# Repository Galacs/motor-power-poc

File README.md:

# Motor Power POC

Motor Power POC board made to test power protection circuits (OCP, UVLO, OVL, RPP...), high current step-down power supply design, rf switch connectors, external FETs H-bridge and power muxes.

## IC List

- ESP32-S3Fx (Main MCU)
- QRE1113 (reflectance sensor)
- LM74502H (Vin RPP)
- TPS56A37 (12v Vout 10A)
- TPS5430 (5v Vout 2.5A)
- LDL212 (3v3 LDO)
- CJ431 (3v shunt reference)
- TPS2121 (5v power mux)
- DRV8701 (H-bridge gate driver)
- SIS412DN-T1-GE3 (10A MOSFET)

## Top preview

## Preview 3d render

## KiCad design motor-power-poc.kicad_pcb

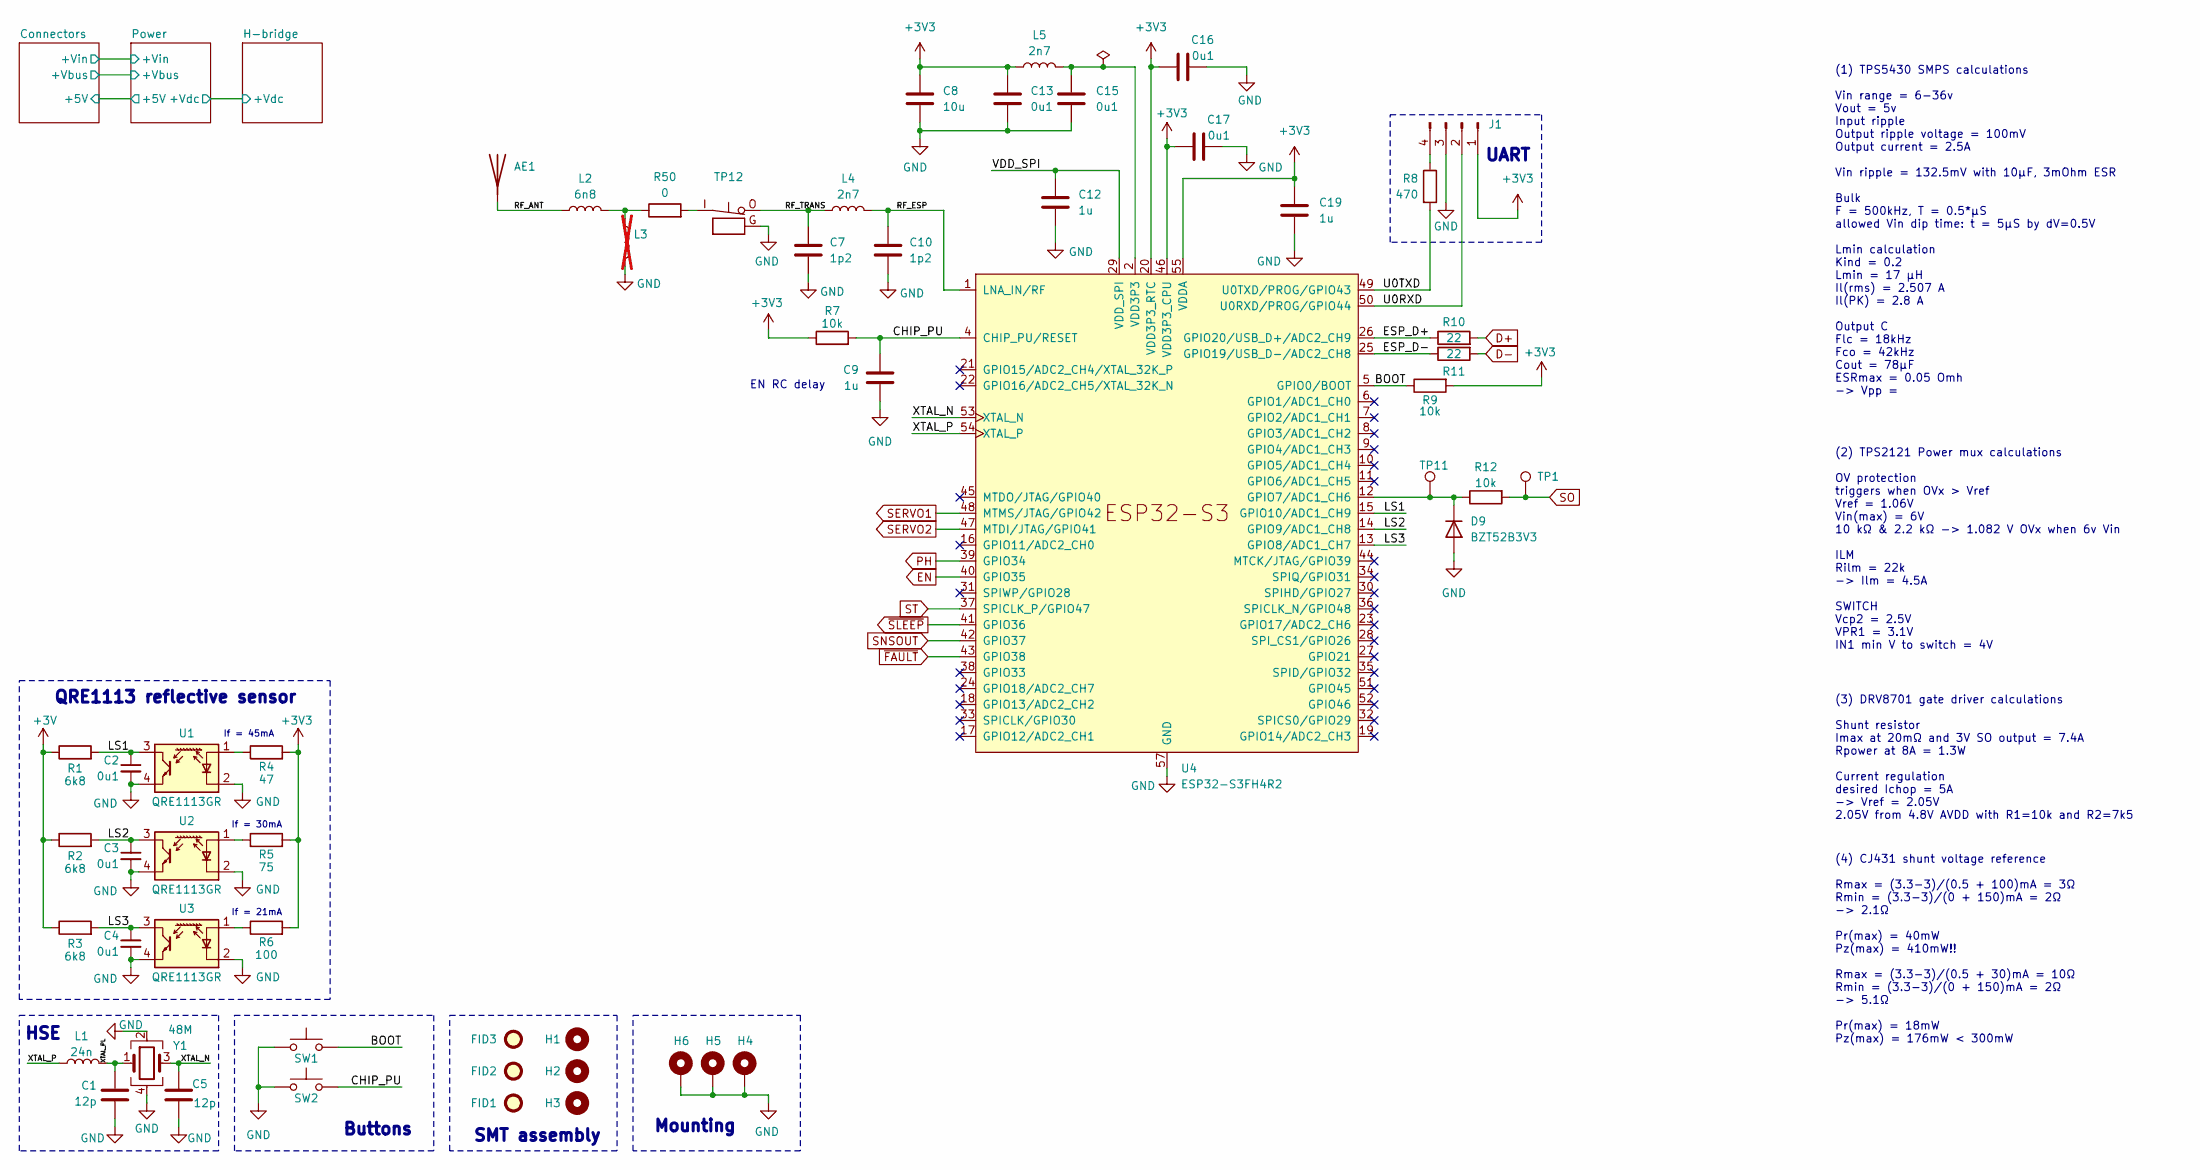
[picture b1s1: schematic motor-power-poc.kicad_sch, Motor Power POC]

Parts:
AE1: Antenna; Johanson_2450AT18x100; Manufacturer Part Number RFANT3216120A5T; JLCPCB Part # C127629
C1, C5: 12p; C_0402_1005Metric; Manufacturer Part Number 0402CG120J500NT; JLCPCB Part # C1547
C2, C3, C4, C13, C15, C16, C17: 0u1; C_0402_1005Metric; Manufacturer Part Number CL05B104KB54PNC; JLCPCB Part # C307331
C7, C10: 1p2; C_0402_1005Metric; Manufacturer Part Number GJM1555C1H1R2WB01D; JLCPCB Part # C76899
C8: 10u; C_0402_1005Metric; Manufacturer Part Number CL05A106MQ5NUNC; JLCPCB Part # C15525
C9, C12, C19: 1u; C_0402_1005Metric; Manufacturer Part Number CL05A105KA5NQNC; JLCPCB Part # C52923
D9: BZT52B3V3; D_SOD-123; Manufacturer Part Number BZT52B3V3; JLCPCB Part # C19077392
FID1, FID2, FID3: Fiducial; Fiducial_1mm_Mask2mm
H1, H2, H3: MountingHole; ToolingHole_1.152mm
H4, H5, H6: MountingHole_Pad; MountingHole_2.2mm_M2_Pad_Via
J1: Conn_01x04_Pin; PinHeader_1x04_P2.54mm_Vertical
L1: 24n; L_0402_1005Metric; Manufacturer Part Number LQW15AN24NG00D; JLCPCB Part # C167472
L2: 6n8; L_0402_1005Metric; Manufacturer Part Number LQG15HS6N8J02D; JLCPCB Part # C77110
L3: L; L_0402_1005Metric; not fitted
L4, L5: 2n7; L_0402_1005Metric; Manufacturer Part Number LQG15HS2N7S02D; JLCPCB Part # C77108
R1, R2, R3: 6k8; R_0603_1608Metric; Manufacturer Part Number 0603WAF6801T5E; JLCPCB Part # C23212
R4: 47; R_0603_1608Metric; Manufacturer Part Number 0603WAF470JT5E; JLCPCB Part # C23182
R5: 75; R_0603_1608Metric; Manufacturer Part Number 0603WAF750JT5E; JLCPCB Part # C4275
R6: 100; R_0603_1608Metric; Manufacturer Part Number 0603WAF1000T5E; JLCPCB Part # C22775
R7, R9, R12: 10k; R_0402_1005Metric; Manufacturer Part Number 0402WGF1002TCE; JLCPCB Part # C25744
R8: 470; R_0402_1005Metric; Manufacturer Part Number 0402WGF4700TCE; JLCPCB Part # C25117
R10, R11: 22; R_0402_1005Metric; Manufacturer Part Number 0402WGF220JTCE; JLCPCB Part # C25092
R50: 0; R_0402_1005Metric; Manufacturer Part Number 0402WGF0000TCE; JLCPCB Part # C17168
SW1, SW2: SW_Push; SW_SPST_TS-1088-xR020; Manufacturer Part Number TS-1088-AR02016; JLCPCB Part # C720477
TP1, TP11: TestPoint; TestPoint_Keystone_5015_Micro_Mini; Manufacturer Part Number 5015; JLCPCB Part # C2906768
TP12: RF_switch_connector; Murata_MM8030-26102610; Manufacturer Part Number MM8030-2610RK0; JLCPCB Part # C91632
U1, U2, U3: QRE1113GR; OnSemi_CASE100CY; Manufacturer Part Number QRE1113GR; JLCPCB Part # C232862
U4: ESP32-S3FH4R2; QFN-56-1EP_7x7mm_P0.4mm_EP4x4mm_ThermalVias; Manufacturer Part Number ESP32-S3FH4R2; JLCPCB Part # C3013940
Y1: 48M; Crystal_SMD_2016-4Pin_2.0x1.6mm; Manufacturer Part Number R940000096; JLCPCB Part # C7206306

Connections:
+3V: R1.1, R2.1, R3.1; also elsewhere on the board
+3V3: C8.1, C13.1, C16.1, C17.1, C19.1, J1.1, L5.1, R4.2, R5.2, R6.2, R7.1, R9.2, U4.20 (VDD3P3_RTC), U4.46 (VDD3P3_CPU), U4.55 (VDDA), U4.56 (VDDA); also elsewhere on the board
/BOOT: R9.1, SW1.2, U4.5 (GPIO0/BOOT)
/CHIP_PU: C9.1, R7.2, SW2.2, U4.4 (CHIP_PU/RESET)
/ESP_D+: R10.1, U4.26 (GPIO20/USB_D+/ADC2_CH9)
/ESP_D-: R11.1, U4.25 (GPIO19/USB_D-/ADC2_CH8)
/LS1: C2.1, R1.2, U1.3, U4.15 (GPIO10/ADC1_CH9)
/LS2: C3.1, R2.2, U2.3, U4.14 (GPIO9/ADC1_CH8)
/LS3: C4.1, R3.2, U3.3, U4.13 (GPIO8/ADC1_CH7)
/RF_ANT: AE1.1 (A), L2.1
/RF_ESP: C10.1, L4.2, U4.1 (LNA_IN/RF)
/RF_TRANS: C7.1, L4.1, TP12.O
/U0RXD: J1.2, U4.50 (U0RXD/PROG/GPIO44)
/U0TXD: R8.2, U4.49 (U0TXD/PROG/GPIO43)
/VDD_SPI: C12.1, U4.29 (VDD_SPI)
/XTAL_N: C5.1, U4.53 (XTAL_N), Y1.3
/XTAL_P: L1.1, U4.54 (XTAL_P)
/XTAL_PL: C1.2, L1.2, Y1.1
D+: R10.2; also elsewhere on the board
D-: R11.2; also elsewhere on the board
EN: U4.40 (GPIO35); also elsewhere on the board
GND: C1.1, C2.2, C3.2, C4.2, C5.2, C7.2, C8.2, C9.2, C10.2, C12.2, C13.2, C15.2, C16.2, C17.2, C19.2, D9.2 (A), H4.1, H5.1, H6.1, J1.3, L3.2, SW1.1, SW2.1, TP12.G, U1.2 (K), U1.4, U2.2 (K), U2.4, U3.2 (K), U3.4, U4.57 (GND), Y1.2, Y1.4; also elsewhere on the board
unnamed: D9.1 (K), R12.1, TP11.1, U4.12 (GPIO7/ADC1_CH6)
unnamed: J1.4, R8.1
unnamed: L2.2, L3.1, R50.1
unnamed: R50.2, TP12.I
unnamed: R4.1, U1.1 (A)
unnamed: R5.1, U2.1 (A)
unnamed: R6.1, U3.1 (A)
PH: U4.39 (GPIO34); also elsewhere on the board
SERVO1: U4.48 (MTMS/JTAG/GPIO42); also elsewhere on the board
SERVO2: U4.47 (MTDI/JTAG/GPIO41); also elsewhere on the board
SNSOUT: U4.42 (GPIO37); also elsewhere on the board
SO: R12.2, TP1.1; also elsewhere on the board
ST: U4.37 (SPICLK_P/GPIO47); also elsewhere on the board
VDD3P3: C15.1, L5.2, U4.2 (VDD3P3), U4.3 (VDD3P3)
~FAULT: U4.43 (GPIO38); also elsewhere on the board
~SLEEP: U4.41 (GPIO36); also elsewhere on the board

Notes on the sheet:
SMT assembly
Mounting
If = 30mA
Buttons
EN RC delay
QRE1113 reflective sensor
If = 45mA
HSE
UART
If = 21mA
(3) DRV8701 gate driver calculations Shunt resistor Imax at 20mΩ and 3V SO output = 7.4A Rpower at 8A = 1.3W Current regulation desired Ichop = 5A -> Vref = 2.05V 2.05V from 4.8V AVDD with R1=10k and R2=7k5
(1) TPS5430 SMPS calculations Vin range = 6-36v Vout = 5v Input ripple Output ripple voltage = 100mV Output current = 2.5A Vin ripple = 132.5mV with 10µF, 3mOhm ESR Bulk F = 500kHz, T = 0.5*µS allowed Vin dip time: t = 5µS by dV=0.5V Lmin calculation Kind = 0.2 Lmin = 17 µH Il(rms) = 2.507 A Il(PK)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
(4) CJ431 shunt voltage reference Rmax = (3.3-3)/(0.5 + 100)mA = 3Ω Rmin = (3.3-3)/(0 + 150)mA = 2Ω -> 2.1Ω Pr(max) = 40mW Pz(max) = 410mW!! Rmax = (3.3-3)/(0.5 + 30)mA = 10Ω Rmin = (3.3-3)/(0 + 150)mA = 2Ω -> 5.1Ω Pr(max) = 18mW Pz(max) = 176mW < 300mW
(2) TPS2121 Power mux calculations OV protection triggers when OVx > Vref Vref = 1.06V Vin(max) = 6V 10 kΩ & 2.2 kΩ -> 1.082 V OVx when 6v Vin ILM Rilm = 22k -> Ilm = 4.5A SWITCH Vcp2 = 2.5V VPR1 = 3.1V IN1 min V to switch = 4V

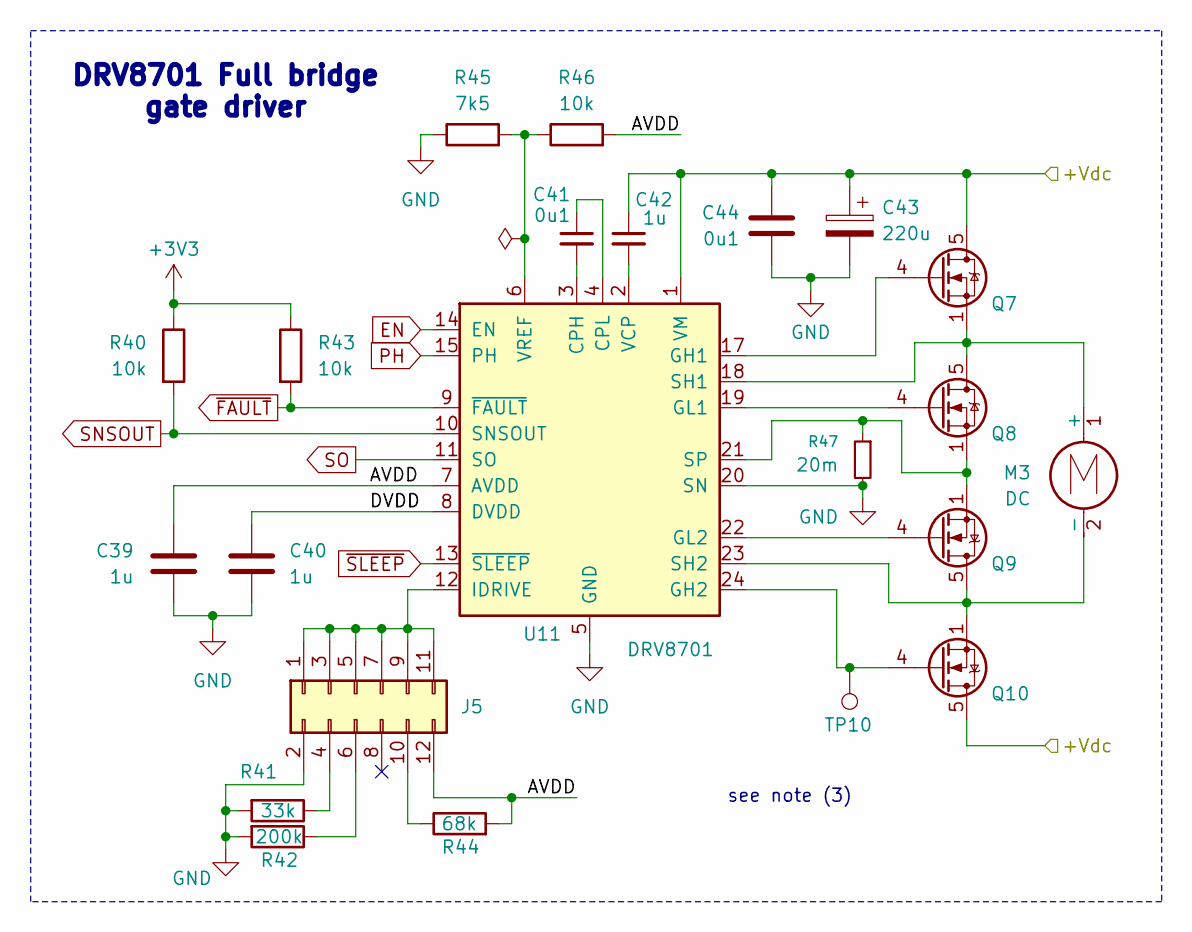
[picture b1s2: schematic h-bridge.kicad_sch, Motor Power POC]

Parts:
C39, C40, C42: 1u; C_0402_1005Metric; Manufacturer Part Number CL05A105KA5NQNC; JLCPCB Part # C52923
C41, C44: 0u1; C_0402_1005Metric; Manufacturer Part Number CL05B104KB54PNC; JLCPCB Part # C307331
C43: 220u; CP_Elec_6.3x7.7; Manufacturer Part Number JVJ35V220M6x8; JLCPCB Part # C46550411
J5: Conn_02x06_Counter_Clockwise; PinHeader_2x06_P2.54mm_Vertical
M3: DC; TerminalBlock_Phoenix_MKDS-1,5-2-5.08_1x02_P5.08mm_Horizont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
Q7, Q8, Q9, Q10: Q_NMOS; Vishay_PowerPAK_1212-8_Single; Manufacturer Part Number SIS412DN-T1-GE3; JLCPCB Part # C111309
R40, R43, R46: 10k; R_0402_1005Metric; Manufacturer Part Number 0402WGF1002TCE; JLCPCB Part # C25744
R41: 33k; R_0402_1005Metric; Manufacturer Part Number 0402WGF3302TCE; JLCPCB Part # C25779
R42: 200k; R_0402_1005Metric; Manufacturer Part Number 0402WGF2003TCE; JLCPCB Part # C25764
R44: 68k; R_0402_1005Metric; Manufacturer Part Number 0402WGF6802TCE; JLCPCB Part # C36871
R45: 7k5; R_0603_1608Metric; Manufacturer Part Number 0603WAF7501T5E; JLCPCB Part # C23234
R47: 20m; R_2512_6332Metric; Manufacturer Part Number HoYLR2512-3W-20mR-1%; JLCPCB Part # C5375467
TP10: TestPoint; TestPoint_Keystone_5015_Micro_Mini; Manufacturer Part Number 5015; JLCPCB Part # C2906768
U11: DRV8701; Texas_RGE0024H_VQFN-24-1EP_4x4mm_P0.5mm_EP2.7x2.7mm_Thermal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; Manufacturer Part Number DRV8701ERGER; JLCPCB Part # C90964

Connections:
+3V3: R40.1, R43.1; also elsewhere on the board
/H-bridge/+Vdc: C42.1, C43.1, C44.1, Q7.5 (D), Q10.5 (D), U11.1 (VM); also elsewhere on the board
/H-bridge/AVDD: C39.1, J5.12, R44.2, R46.2, U11.7 (AVDD)
/H-bridge/DVDD: C40.1, U11.8 (DVDD)
EN: U11.14 (EN); also elsewhere on the board
GND: C39.2, C40.2, C43.2, C44.2, J5.2, R41.2, R42.2, R45.1, R47.2, U11.5 (GND), U11.16 (GND), U11.20 (SN), U11.25 (GND); also elsewhere on the board
unnamed: J5.1, J5.3, J5.5, J5.7, J5.9, J5.11, U11.12 (IDRIVE)
unnamed: J5.4, R41.1
unnamed: J5.6, R42.1
unnamed: J5.10, R44.1
unnamed: M3.1 (+), Q7.1 (S), Q7.2 (S), Q7.3 (S), Q8.5 (D), U11.18 (SH1)
unnamed: M3.2 (-), Q9.5 (D), Q10.1 (S), Q10.2 (S), Q10.3 (S), U11.23 (SH2)
unnamed: Q7.4 (G), U11.17 (GH1)
unnamed: Q8.4 (G), U11.19 (GL1)
unnamed: Q9.4 (G), U11.22 (GL2)
unnamed: Q10.4 (G), TP10.1, U11.24 (GH2)
unnamed: C41.2, U11.3 (CPH)
unnamed: C41.1, U11.4 (CPL)
unnamed: Q8.1 (S), Q8.2 (S), Q8.3 (S), Q9.1 (S), Q9.2 (S), Q9.3 (S), R47.1, U11.21 (SP)
unnamed: C42.2, U11.2 (VCP)
unnamed: R45.2, R46.1, U11.6 (VREF)
PH: U11.15 (PH); also elsewhere on the board
SNSOUT: R40.2, U11.10 (SNSOUT); also elsewhere on the board
SO: U11.11 (SO); also elsewhere on the board
~FAULT: R43.2, U11.9 (~FAULT); also elsewhere on the board
~SLEEP: U11.13 (~SLEEP); also elsewhere on the board

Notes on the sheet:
see note (3)
DRV8701 Full bridge gate driver

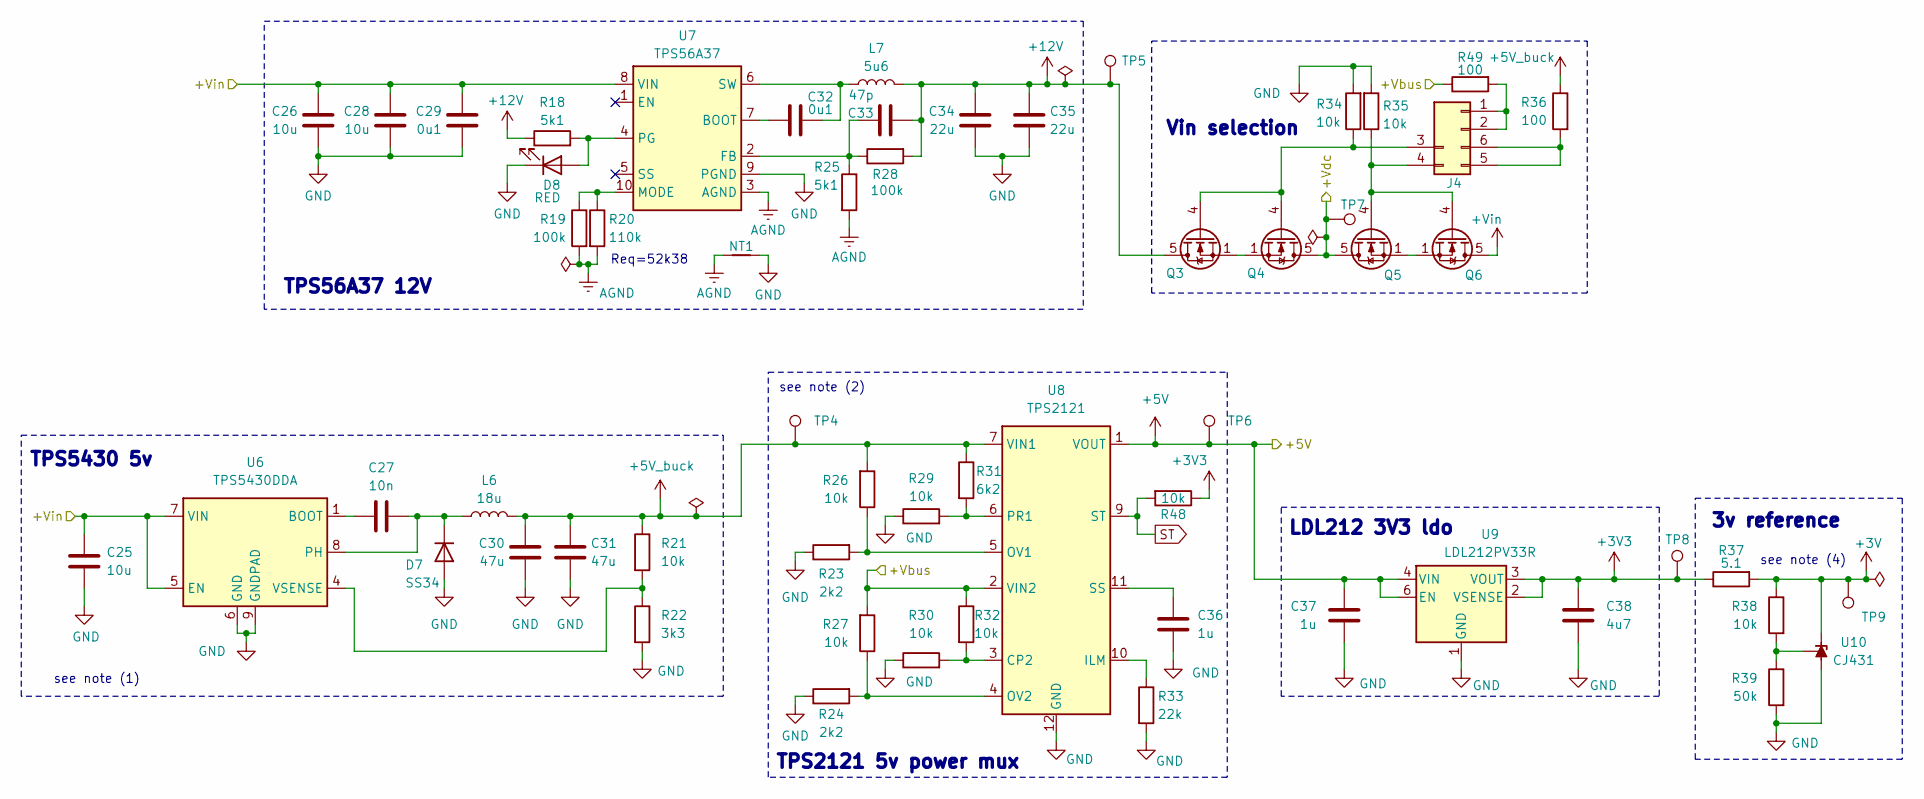
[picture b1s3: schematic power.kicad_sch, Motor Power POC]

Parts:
C25, C26, C28: 10u; C_0805_2012Metric; Manufacturer Part Number GRM21BR61H106KE43L; JLCPCB Part # C440198
C27: 10n; C_0402_1005Metric; Manufacturer Part Number CL05B103KB5NNNC; JLCPCB Part # C15195
C29, C32: 0u1; C_0402_1005Metric; Manufacturer Part Number CL05B104KB54PNC; JLCPCB Part # C307331
C30, C31: 47u; C_1206_3216Metric; Manufacturer Part Number CL31A476MPHNNNE; JLCPCB Part # C96123
C33: 47p; C_0402_1005Metric; Manufacturer Part Number 0402CG470J500NT; JLCPCB Part # C1567
C34, C35: 22u; C_0805_2012Metric; Manufacturer Part Number CL21A226MAQNNNE; JLCPCB Part # C45783
C36, C37: 1u; C_0402_1005Metric; Manufacturer Part Number CL05A105KA5NQNC; JLCPCB Part # C52923
C38: 4u7; C_0402_1005Metric; Manufacturer Part Number CL05A475MP5NRNC; JLCPCB Part # C23733
D7: SS34; D_SMA; Manufacturer Part Number SS34; JLCPCB Part # C8678
D8: RED; LED_0603_1608Metric; Manufacturer Part Number KT-0603R; JLCPCB Part # C2286
J4: Conn_02x02_Counter_Clockwise; PinHeader_2x03_P2.54mm_Vertical
L6: 18u; L_Sunlord_SWRB1207S; Manufacturer Part Number SWRH1207B-180MT; JLCPCB Part # C73501
L7: 5u6; L_Sunlord_MWSA0804S; Manufacturer Part Number MWSA0804S-5R6MT; JLCPCB Part # C17700168
NT1: NetTie_2; NetTie-2_SMD_Pad0.5mm
Q3, Q4, Q5, Q6: Q_NMOS; Vishay_PowerPAK_1212-8_Single; Manufacturer Part Number SIS412DN-T1-GE3; JLCPCB Part # C111309
R18, R25: 5k1; R_0402_1005Metric; Manufacturer Part Number 0402WGF5101TCE; JLCPCB Part # C25905
R19, R28: 100k; R_0402_1005Metric; Manufacturer Part Number 0402WGF1003TCE; JLCPCB Part # C25741
R20: 110k; R_0603_1608Metric; Manufacturer Part Number 0603WAF1103T5E; JLCPCB Part # C25805
R21, R26, R27, R29, R30, R32, R34, R35, R48: 10k; R_0402_1005Metric; Manufacturer Part Number 0402WGF1002TCE; JLCPCB Part # C25744
R22: 3k3; R_0402_1005Metric; Manufacturer Part Number 0402WGF3301TCE; JLCPCB Part # C25890
R23, R24: 2k2; R_0402_1005Metric; Manufacturer Part Number 0402WGF2201TCE; JLCPCB Part # C25879
R31: 6k2; R_0603_1608Metric; Manufacturer Part Number 0603WAF6201T5E; JLCPCB Part # C4260
R33: 22k; R_0402_1005Metric; Manufacturer Part Number 0402WGF2202TCE; JLCPCB Part # C25768
R36, R49: 100; R_0603_1608Metric; Manufacturer Part Number 0603WAF1000T5E; JLCPCB Part # C22775
R37: 5.1; R_0805_2012Metric; Manufacturer Part Number 0805W8F510KT5E; JLCPCB Part # C17724
R38: 10k; R_0603_1608Metric; Manufacturer Part Number 0603WAF1002T5E; JLCPCB Part # C25804
R39: 50k; R_0603_1608Metric; Manufacturer Part Number 0603WAF4992T5E; JLCPCB Part # C23184
TP4, TP5, TP6, TP7, TP8, TP9: TestPoint; TestPoint_Keystone_5015_Micro_Mini; Manufacturer Part Number 5015; JLCPCB Part # C2906768
U6: TPS5430DDA; TI_SO-PowerPAD-8_ThermalVias; Manufacturer Part Number TPS5430DDAR; JLCPCB Part # C9864
U7: TPS56A37; Texas_RPA0010A_VQFN-HR-10_3x3mm_P0.5mm; Manufacturer Part Number TPS56A37RPAR; JLCPCB Part # C22392669
U8: TPS2121; Texas_VQFN-HR-12_2x2.5mm_P0.5mm; Manufacturer Part Number TPS2121RUXR; JLCPCB Part # C485916
U9: LDL212PV33R; DFN-6-1EP_2x2mm_P0.5mm_ST; Manufacturer Part Number LDL212PV33R; JLCPCB Part # C2969892
U10: CJ431; SOT-23; Manufacturer Part Number CJ431; JLCPCB Part # C3113

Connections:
+3V: R37.2, R38.1, TP9.1, U10.2 (K); also elsewhere on the board
+3V3: C38.1, R37.1, R48.1, TP8.1, U9.2 (VSENSE), U9.3 (VOUT); also elsewhere on the board
+5V: C37.1, TP6.1, U8.1 (VOUT), U8.8 (VOUT), U9.4 (VIN), U9.6 (EN); also elsewhere on the board
+5V_buck: C30.1, C31.1, L6.2, R21.1, R26.2, R31.1, R36.1, TP4.1, U8.7 (VIN1)
+12V: C33.2, C34.1, C35.1, L7.2, Q3.5 (D), R18.1, R28.2, TP5.1
+Vbus: R27.2, R32.1, R49.1, U8.2 (VIN2); also elsewhere on the board
+Vin: C25.1, C26.1, C28.1, C29.1, Q6.5 (D), U6.5 (EN), U6.7 (VIN), U7.8 (VIN); also elsewhere on the board
/H-bridge/+Vdc: Q4.5 (D), Q5.5 (D), TP7.1; also elsewhere on the board
AGND: NT1.1, R19.2, R20.2, R25.2, U7.3 (AGND)
GND: C25.2, C26.2, C28.2, C29.2, C30.2, C31.2, C34.2, C35.2, C36.2, C37.2, C38.2, D7.2 (A), D8.1 (K), NT1.2, R22.2, R23.1, R24.1, R29.1, R30.1, R33.2, R34.2, R35.2, R39.2, U6.6 (GND), U6.9 (GNDPAD), U7.9 (PGND), U8.12 (GND), U9.1 (GND), U10.3 (A); also elsewhere on the board
unnamed: C27.2, D7.1 (K), L6.1, U6.8 (PH)
unnamed: D8.2 (A), R18.2, U7.4 (PG)
unnamed: J4.1, J4.2, R49.2
unnamed: J4.3, Q3.4 (G), Q4.4 (G), R34.1
unnamed: J4.4, Q5.4 (G), Q6.4 (G), R35.1
unnamed: J4.5, J4.6, R36.2
unnamed: Q3.1 (S), Q3.2 (S), Q3.3 (S), Q4.1 (S), Q4.2 (S), Q4.3 (S)
unnamed: Q5.1 (S), Q5.2 (S), Q5.3 (S), Q6.1 (S), Q6.2 (S), Q6.3 (S)
unnamed: C27.1, U6.1 (BOOT)
unnamed: R21.2, R22.1, U6.4 (VSENSE)
unnamed: C32.1, U7.7 (BOOT)
unnamed: C33.1, R25.1, R28.1, U7.2 (FB)
unnamed: R19.1, R20.1, U7.10 (MODE)
unnamed: C32.2, L7.1, U7.6 (SW)
unnamed: R30.2, R32.2, U8.3 (CP2)
unnamed: R33.1, U8.10 (ILM)
unnamed: R23.2, R26.1, U8.5 (OV1)
unnamed: R24.2, R27.1, U8.4 (OV2)
unnamed: R29.2, R31.2, U8.6 (PR1)
unnamed: C36.1, U8.11 (SS)
unnamed: R38.2, R39.1, U10.1 (REF)
ST: R48.2, U8.9 (ST); also elsewhere on the board

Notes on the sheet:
Vin selection
3v reference
TPS2121 5v power mux
LDL212 3V3 ldo
see note (1)
see note (2)
Req=52k38
TPS5430 5v
TPS56A37 12V
see note (4)

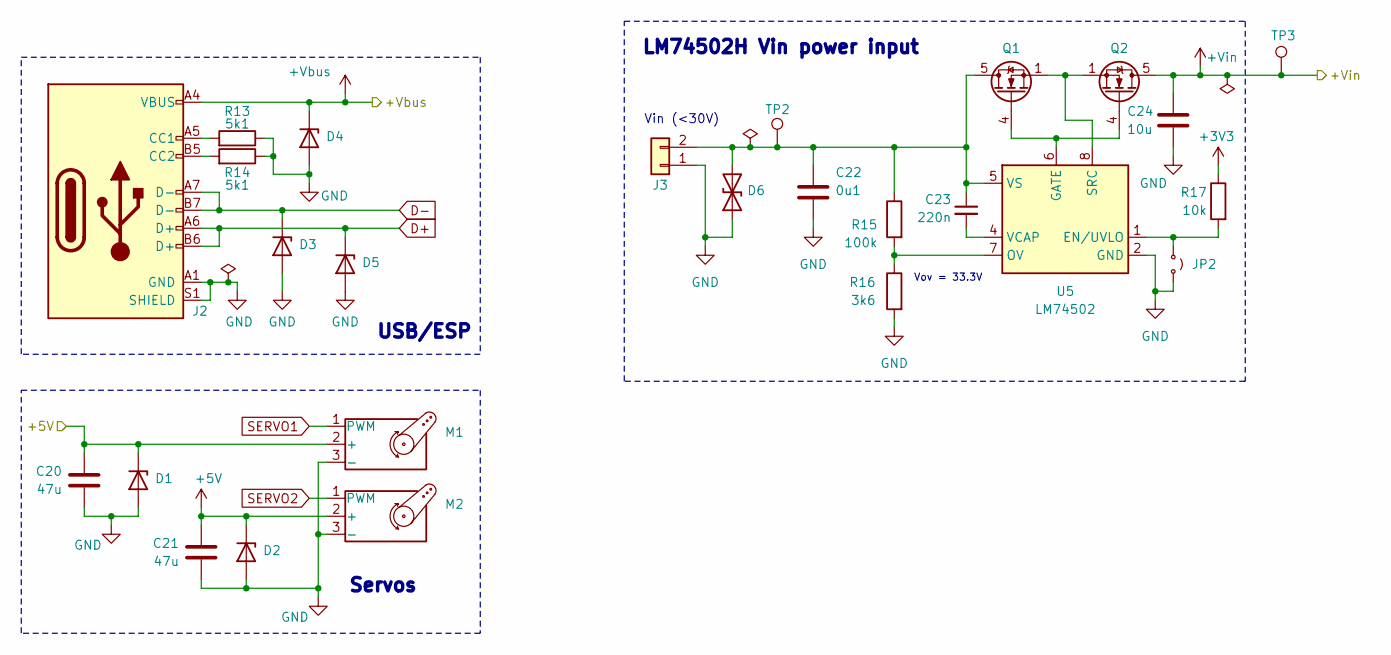
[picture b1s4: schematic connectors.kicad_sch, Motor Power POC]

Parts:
C20, C21: 47u; C_1206_3216Metric; Manufacturer Part Number CL31A476MPHNNNE; JLCPCB Part # C96123
C22: 0u1; C_0402_1005Metric; Manufacturer Part Number CL05B104KB54PNC; JLCPCB Part # C307331
C23: 220n; C_0402_1005Metric; Manufacturer Part Number CL05B224KO5NNNC; JLCPCB Part # C16772
C24: 10u; C_0805_2012Metric; Manufacturer Part Number GRM21BR61H106KE43L; JLCPCB Part # C440198
D1, D2, D3, D4, D5: H5VU10U; Diode_DFN1006; Manufacturer Part Number H5VU10U; JLCPCB Part # C22395519
D6: D_TVS; D_SMB; Manufacturer Part Number SMBJ30CA; JLCPCB Part # C2925441
J2: USB_C_Receptacle_USB2.0_14P; USB_C_Receptacle_HRO_TYPE-C-31-M-12; Manufacturer Part Number TYPE-C16PIN; JLCPCB Part # C393939
J3: Conn_01x02; TerminalBlock_Phoenix_MKDS-1,5-2-5.08_1x02_P5.08mm_Horizont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
JP2: Jumper_2_Small_Open; PinHeader_1x02_P2.54mm_Vertical
M1, M2: Motor_Servo; PinHeader_1x03_P2.54mm_Vertical
Q1, Q2: Q_NMOS; Vishay_PowerPAK_1212-8_Single; Manufacturer Part Number SIS412DN-T1-GE3; JLCPCB Part # C111309
R13, R14: 5k1; R_0402_1005Metric; Manufacturer Part Number 0402WGF5101TCE; JLCPCB Part # C25905
R15: 100k; R_0402_1005Metric; Manufacturer Part Number 0402WGF1003TCE; JLCPCB Part # C25741
R16: 3k6; R_0603_1608Metric; Manufacturer Part Number 0603WAF3601T5E; JLCPCB Part # C22980
R17: 10k; R_0402_1005Metric; Manufacturer Part Number 0402WGF1002TCE; JLCPCB Part # C25744
TP2, TP3: TestPoint; TestPoint_Keystone_5015_Micro_Mini; Manufacturer Part Number 5015; JLCPCB Part # C2906768
U5: LM74502; SOT-23-THIN-8; Manufacturer Part Number LM74502DDFR; JLCPCB Part # C3236215

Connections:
+3V3: R17.1; also elsewhere on the board
+5V: C20.1, C21.1, D1.1 (K), D2.1 (K), M1.2 (+), M2.2 (+); also elsewhere on the board
+Vbus: D4.1 (K), J2.A4 (VBUS), J2.A9 (VBUS), J2.B4 (VBUS), J2.B9 (VBUS); also elsewhere on the board
+Vin: C24.1, Q2.5 (D), TP3.1; also elsewhere on the board
D+: D5.1 (K), J2.A6 (D+), J2.B6 (D+); also elsewhere on the board
D-: D3.1 (K), J2.A7 (D-), J2.B7 (D-); also elsewhere on the board
GND: C20.2, C21.2, C22.2, C24.2, D1.2 (A), D2.2 (A), D3.2 (A), D4.2 (A), D5.2 (A), D6.1 (A1), J2.A1 (GND), J2.A12 (GND), J2.B1 (GND), J2.B12 (GND), J2.S1 (SHIELD), J3.1, JP2.2 (B), M1.3 (-), M2.3 (-), R13.1, R14.1, R16.2, U5.2 (GND); also elsewhere on the board
unnamed: C22.1, C23.1, D6.2 (A2), J3.2, Q1.5 (D), R15.1, TP2.1, U5.5 (VS)
unnamed: J2.A5 (CC1), R13.2
unnamed: J2.B5 (CC2), R14.2
unnamed: JP2.1 (A), R17.2, U5.1 (EN/UVLO)
unnamed: Q1.4 (G), Q2.4 (G), U5.6 (GATE)
unnamed: R15.2, R16.1, U5.7 (OV)
unnamed: Q1.1 (S), Q1.2 (S), Q1.3 (S), Q2.1 (S), Q2.2 (S), Q2.3 (S), U5.8 (SRC)
unnamed: C23.2, U5.4 (VCAP)
SERVO1: M1.1 (PWM); also elsewhere on the board
SERVO2: M2.1 (PWM); also elsewhere on the board

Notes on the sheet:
Vin (<30V)
Vov = 33.3V
LM74502H Vin power input
USB/ESP
Servos

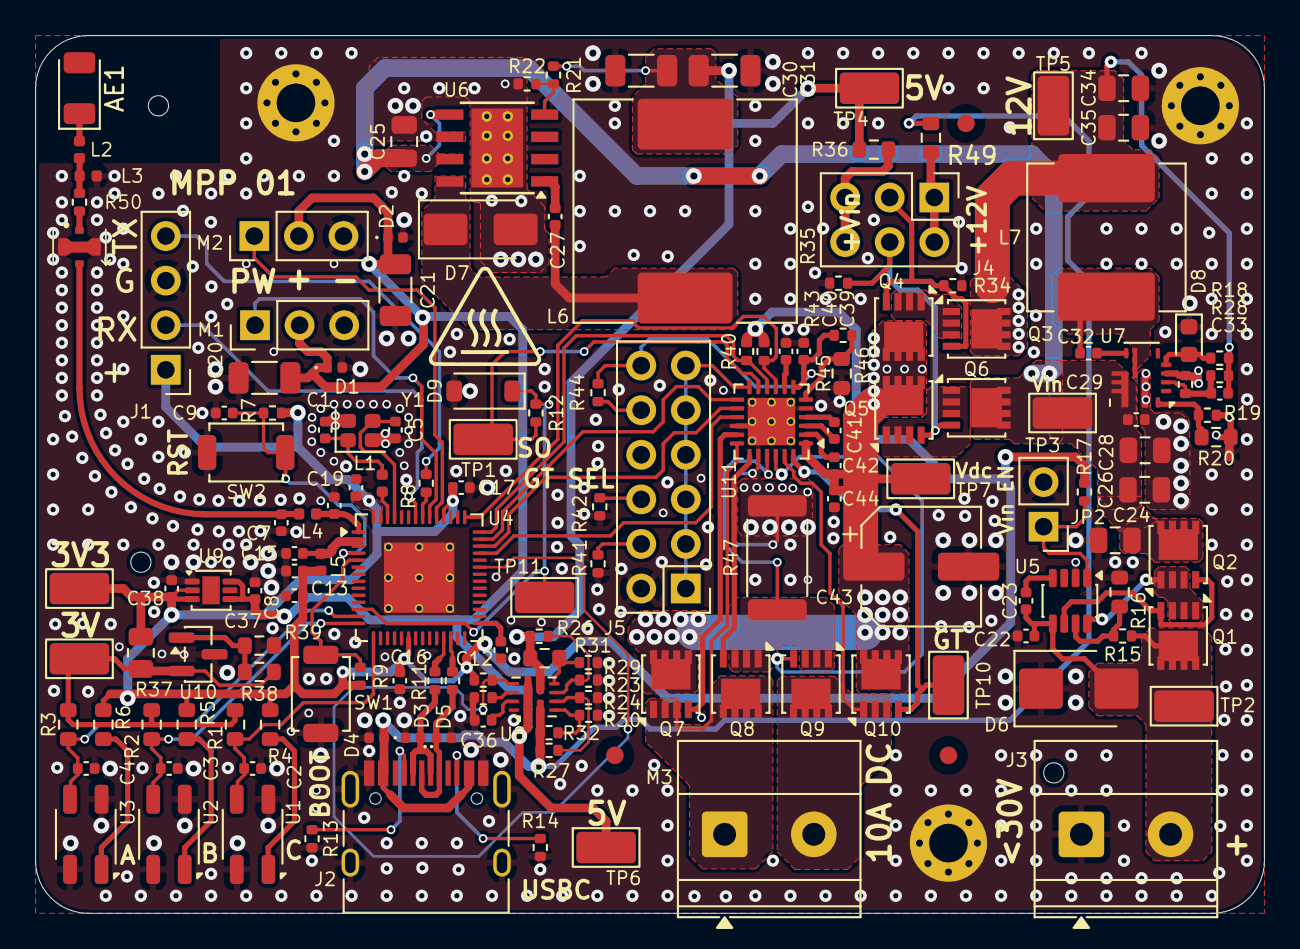
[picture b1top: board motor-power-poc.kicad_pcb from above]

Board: 4 copper layers, 70.0 x 50.0 mm, 162 parts (0 on the bottom side), 91 nets.

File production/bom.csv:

Designator,Footprint,Quantity,Value,LCSC Part #
AE1,Johanson_2450AT18x100,1,Antenna,C89334
"C1, C5",0402,2,12p,C1547
"C10, C7",0402,2,1p2,C76899
"C12, C19, C36, C37, C39, C40, C42, C9",0402,8,1u,C52923
"C13, C15, C16, C17, C2, C22, C29, C3, C32, C4, C41, C44",0402,12,0u1,C307331
"C20, C21, C30, C31",1206,4,47u,C96123
C23,0402,1,220n,C16772
"C24, C25, C26, C28",0805,4,10u,C440198
C27,0402,1,10n,C15195
C33,0402,1,47p,C1567
"C34, C35",0805,2,22u,C45783
C38,0402,1,4u7,C23733
C43,CP_Elec_6.3x7.7,1,220u,C46550411
C6,0402,1,1p,C1550
C8,0402,1,10u,C15525
"D1, D2, D3, D4, D5",Diode_DFN1006,5,H5VU10U,C22395519
D6,D_SMB,1,D_TVS,C2925441
D7,D_SMA,1,SS34,C8678
D8,0603,1,RED,C2286
D9,D_SOD-123,1,BZT52B3V3,C19077392
J2,USB_C_Receptacle_HRO_TYPE-C-31-M-12,1,USB_C_Receptacle_USB2.0_14P,C393939
L1,0402,1,24n,C167472
L2,0402,1,3n9,C77109
"L3, L4, L5",0402,3,2n7,C77108
L6,L_Sunlord_SWRB1207S,1,18u,C73501
L7,L_Sunlord_MWSA0804S,1,5u6,C17700168
"Q1, Q10, Q2, Q3, Q4, Q5, Q6, Q7, Q8, Q9",Vishay_PowerPAK_1212-8_Single,10,Q_NMOS,C111309
"R1, R2, R3",0603,3,6k8,C23212
"R10, R11",0402,2,22,C25092
"R12, R17, R21, R26, R27, R29, R30, R32, R34, R35, R40, R43, R46, R48, R7, R9",0402,16,10k,C25744
"R13, R14, R18, R25",0402,4,5k1,C25905
"R15, R19, R28",0402,3,100k,C25741
R16,0603,1,3k6,C22980
R20,0603,1,110k,C25805
R22,0402,1,3k3,C25890
"R23, R24",0402,2,2k2,C25879
R31,0603,1,6k2,C4260
R33,0402,1,22k,C25768
"R36, R6",0603,2,100,C22775
R37,0805,1,5.1,C17724
R38,0603,1,10k,C25804
R39,0603,1,50k,C23184
R4,0603,1,47,C23182
R41,0402,1,33k,C25779
R42,0402,1,200k,C25764
R44,0402,1,68k,C36871
R45,0603,1,7k5,C23234
R47,2512,1,20m,C5375467
R5,0603,1,75,C4275
R8,0402,1,470,C25117
"SW1, SW2",SW_SPST_TS-1088-xR020,2,SW_Push,C720477
"TP1, TP10, TP11, TP2, TP3, TP4, TP5, TP6, TP7, TP8, TP9",TestPoint_Keystone_5015_Micro_Mini,11,TestPoint,C2906768
"U1, U2, U3",OnSemi_CASE100CY,3,QRE1113GR,C232862
U10,SOT-23,1,CJ431,C3113
U11,Texas_RGE0024H_VQFN-24-1EP_4x4mm_P0.5mm_EP2.7x2.7mm_ThermalVias,1,DRV8701,C90964
U4,QFN-56-1EP_7x7mm_P0.4mm_EP4x4mm_ThermalVias,1,ESP32-S3FH4R2,C3013940
U5,SOT-23-THIN-8,1,LM74502,C3236215
U6,TI_SO-PowerPAD-8_ThermalVias,1,TPS5430DDA,C9864
U7,Texas_RPA0010A_VQFN-HR-10_3x3mm_P0.5mm,1,TPS56A37,C22392669
U8,Texas_VQFN-HR-12_2x2.5mm_P0.5mm,1,TPS2121,C485916
U9,DFN-6-1EP_2x2mm_P0.5mm_ST,1,LDL212PV33R,C2969892
Y1,Crystal_SMD_2016-4Pin_2.0x1.6mm,1,48M,C7206306

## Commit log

2025-11-17 schem: import ESP32-S3 and USBC from adbq-usb-temp
2025-11-18 schem: add TPS5430 5v SMPS with calculations note
2025-11-20 schem: add TPS2121 5v power mux
2025-11-21 schem: add TPS2121 5v power mux components values
2025-11-21 schem: update VBUS TVS diode
2025-11-21 schem: add LDL212 3V3 ldo
2025-11-27 schem: moved connectors to separate sheet
2025-11-27 schem: moved ldo, smps and power mux to power sheet
2025-11-27 symbol: update footprints library name
2025-11-27 schem: add LM74502H Vin power input
2025-11-27 schem: add servos connectors
2025-11-28 schematic: DRV8701 Full bridge gate driver
2025-11-29 schem: add DRV8701 component values
2025-11-29 schem: add LM74502H enable jumper
2025-11-29 schem: add TPS56A37 components values
2025-11-29 schem: add Vin driver input selection circuit
2025-11-29 schem: move selection circuit
2025-11-29 schem: changed selection circuit to back to back fets
2025-11-29 schem: add QRE1113 reflective sensor
2025-11-30 schem: add 3v reference
2025-11-30 schem: add pins to hierachical sheets
2025-11-30 schem: add +Vbus to hierachical
2025-11-30 schem: add +5V to hierachical
2025-11-30 schem: connect dc driver to mcu and add no connects
2025-11-30 schem: add test points
2025-11-30 schem: fix peripherals using flash ESP32 pins
2025-11-30 schem: renumber
2025-11-30 schem: run and fix ERC
2025-11-30 schem: add net classes
2025-11-30 schem: import UART connector from esp32c6-sensor-devboard
2025-11-30 schem: add title
2025-11-30 schem: assign footprints
2025-12-01 schem: add connectors footprint
2025-12-01 schem: add ordering info to BOM
2025-12-02 pcb: create file
2025-12-02 pcb: import 4 layer stackup
2025-12-02 schem: update MOSFETs symbol
2025-12-02 schem: fix DRV8701 gnd pad pin number
2025-12-02 pcb: import from schematic
2025-12-02 pcb: add missing 3d models
2025-12-02 pcb: initial rough placement
2025-12-02 pcb: layout refinement
2025-12-02 schem: update MOSFETs footprints to correct N-channel
2025-12-02 pcb: import predefined sizes
2025-12-02 pcb: add LM74502 RPP layout
2025-12-03 pcb: add TPS56A37 layout
2025-12-03 schem: add 0u1 decoupling cap to DRV8701
2025-12-03 pcb: add DRV8701 layout
2025-12-03 pcb: add 3v3 and 3v layout
2025-12-03 pcb: add QR113 layout
2025-12-03 schem: connect TPS2121 ST pin to MCU
2025-12-03 pcb: add TPS2121 layout
2025-12-03 pcb: add TPS5430 layout
2025-12-03 schem: remove extra decoupling caps
2025-12-03 pcb: add mcu decoupling caps layout
2025-12-03 pcb: add board outline
2025-12-03 schem: add fiduals, tooling and mounting holes
2025-12-03 pcb: add fiducials, tooling holes and mounting holes
2025-12-03 schem: add DRV8701 gate test point
2025-12-03 pcb: add inner gnd planes
2025-12-03 schem: use espressif QFN-56 footprint for ESP32S3 MCU
2025-12-03 pcb: add gns vias
2025-12-03 pcb: set grid and drill origins
2025-12-03 schem: ESP32 pin reorganisation
2025-12-03 pcb: add rf routing
2025-12-03 pcb: add crystal routing
2025-12-03 pcb: add USB routing
2025-12-03 pcb: add UART and servo PWM routing
2025-12-03 pcb: add QR1113 routing
2025-12-03 pcb: add LM74502H RPP routing
2025-12-03 schem: add AGND PGND net tie
2025-12-03 pcb: add TPS56A37 SMPS routing
2025-12-04 pcb: add 3v3 ldo routing
2025-12-04 pcb: add 3v reference routing
2025-12-04 pcb: add AGND net color
2025-12-04 pcb: add CHIP_PU routing
2025-12-04 pcb: add BOOT routing
2025-12-04 pcb: add TPS2121 power mux routing
2025-12-05 pcb: set thermal vias connections to solid
2025-12-05 pcb: add TPS5430 routing
2025-12-05 pcb: add Vin selection routing
2025-12-05 pcb: add DRV8701 routing
2025-12-05 pcb: add 5v routing
2025-12-05 pcb: add outer gnd planes
2025-12-05 pcb: add logic pwr 3V3 routing
2025-12-05 pcb: finish 3v3 power routing
2025-12-05 pcb: add Vin and TPS2121 ST routing
2025-12-05 pcb: remove rf trace soldermask
2025-12-05 pcb: add gnd stitching vias
2025-12-05 schem: remove unnecesary label
2025-12-05 pcb: run and fix DRC
2025-12-05 pcb(silkscreen): clean up reference desginators
2025-12-05 pcb: add title
2025-12-05 pcb: remove unused internal pads
2025-12-06 pcb(silkscreen): add top usr text
2025-12-06 pcb(silkscreen): add bottom usr text
2025-12-06 add production files
2025-12-06 schem: fix BOM
2025-12-06 pcb: set 何何 placeholder
2025-12-10 pcb: move hot warning to avoid exposing Vin
2025-12-10 schem: remove circular dependency for vin sel gate
2025-12-10 pcb: update vin sel from schematic
2025-12-10 pcb(silkscreen): move title up
2025-12-10 schem: change antenna to available and add rf switch connector
2025-12-10 pcb: import new rf components
2025-12-10 regenerate production files
2025-12-11 add README.md
2025-12-11 docs: add preview images to README
